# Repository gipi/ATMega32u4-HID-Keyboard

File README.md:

## ATMega32u4 HID Keyboard

### Board Project 2019 - Krishna Mani

This is software for ATMega32u4 or compatible AVR hardware USB chips that
implements a standard-complying HID keyboard using only AVR-LIBC.

I used these for reference when coding:

1. https://www.avrfreaks.net/forum/usb-initialization-problem
2. https://www.pjrc.com/teensy/usb_keyboard.html
3. https://www.usb.org/sites/default/files/documents/hid1_11.pdf
4. https://www.avrfreaks.net/forum/help-properly-initializing-usb-hardware-atmega32u4
5. https://www.beyondlogic.org/usbnutshell/usb1.shtml
6. http://ww1.microchip.com/downloads/en/devicedoc/atmel-7766-8-bit-avr-atmega16u4-32u4_datasheet.pdf
7. https://github.com/arduino/ArduinoCore-avr/blob/master/cores/arduino/USBCore.cpp
8. http://sdphca.ucsd.edu/lab_equip_manuals/usb_20.pdf

Finished Board:

### Hardware

##### Microcontroller

The ATMega32u4 controls the scanning matrix and the USB interface. I chose it
because of its hardware USB interface and because it has enough I/O pins to
support the whole keyboard without needing any multiplexing. It also has enough
flash and SRAM for storing layouts. The 32u4 on the keyboard runs at 16mHz from
an external crystal oscillator with 22pF load capacitors. It is powered directly
from the USB lines with filtering capacitors.

##### PCBs

Initially, I needed to test the main microcontroller circuit of the keyboard to
ensure that it worked and that the USB worked, because I had developed on an
Arduino Leonardo. (boards/ATMegaTestingBoard.brd)

##### ATMega32u4 Circuit

The portion of the board for the ATMega32u4 is fairly standard for this chip and
is similar to the Arduino Leonardo, excluding the power regulators. It consists
of the chip, the oscillator and load caps, the power and layer leds, the reset
switch, the USB connector and data resistors, the ICSP pins, and the filtering
    caps on the underside of the board.

Top / Bottom (boards/Keyboard.brd):

The rest of the board is the scanning matrix. The rows and columns use up the
majority of the I/O on the chip.  The matrix is standard for a keyboard - one
pin of each switch in a column is connected through a diode to every other one
in the column. Then, the remaining pin in each switch is common with the row. I
used through hole diodes because they are much easier to solder. The switches
are standard mechanical keyboard switches, and the footprints are from here:
https://github.com/mknyszek/gateron-eagle To read the matrix, the row pins are
pulled high through internal pull-up resistors. One column at a time is set low,
so that a pressed key would pull the row pin low, signaling a key press at the
current row and column index.

Top / Bottom matrix (boards/Keyboard.brd):

##### Board Assembly

Assembling the board was straightforward except for the SMD components,
specifically the TQFP ATMega32u4. It is really easy to bridge several pads very
quickly, and completely ruin the chip. I soldered these by holding them in place
and tacking down the corners so the chip didn’t move. I used a lot of flux, then
with very little solder dragged the iron across the pins. The USB connector is
also really difficult, I soldered the anchor pins and then the pins. It is
really easy to bridge the pins with the ground enclosure. Using super glue after
ensures that the connector doesn’t snap off when you unplug the cable.

### Code

To compile you need ``cmake``

```
$ mkdir build && cd build
$ cmake -DCMAKE_TOOLCHAIN_FILE=/path/to/cmake-avr/generic-gcc-avr.cmake ..
$ make
```

##### USB

First, the USB controller of the 32u4 is initialized. This is handled in the
function `usb_init()`. The PLL (Phase Locked Loop) is initialized, taking the
external clock as input. It runs at 48mHz and acts as the USB clock. After the
USB controller is initialized, the control endpoint is set up and will receive
setup packets from the host. The setup packets, handled in the ISR
`USB_gen_vect`, elicit responses from the keyboard based on the values of
bmRequestType and bRequest, which determine the type of request. After the host
has requested and received the USB descriptors, and the keyboard has correctly
responded to HID-specific requests, the host can enumerate the device and use it
as an input device.

The key repeat feature of modern keyboards is handled separately from the
standard functions `usb_send()` and `usb_send_keypress()`. If a key is held down
for some period of time, it should be repeated until it is released. This is
    taken care of in the ISR `USB_gen_vect`, specifically when the SOFE (start
    of frame) bit is set. This interrupt triggers at 1kHz, which is how often
    the host sends start of frame packets. If no keypresses have been generated
    since the period time, which is kept track of with keyboard_idle_value and
    current_idle, the entire HID report is resent to facilitate key repeat. The
    period of time the device should wait before resending the report is set
    from the wValue in the HID request SET_IDLE.

##### Matrix Software

The scanning matrix of the keyboard uses the current sourcing and internal
pullups of the I/O ports on the 32u4. Because of the orientation of the diodes,
the columns of the keyboard are set low when they are going to be read. The rows
are always pulled up, meaning that if a key is pressed, it will be pulled low
because the switch is connecting the row and columns. The matrix scanning is
repeated quickly, and changes in key state are recorded in the six-byte USB HID
report. The report is six bytes to support six concurrent key presses. The
keyboard dynamically assigns and removes keys from the report to support
6-key-rollover, and it also resets the reports on layout layer shifts to prevent
strange glitches. The meta and special keys like CTRL, ALT, and SHIFT have their
own byte apart from the report, where each bit represents a different key. This
is according to the USB HID Spec.

The rows and columns of the recorded keypresses are translated into actual
keycodes from the specified layout in `layout.h`. The layout is written from the
standard HID keycodes in `keys.h`. Because the keyboard does not have enough
physical keys to support all the letters, function, and number keys, some keys
are macros that change the mappings of all the keys. These keys are handled
separately and do not generate keypress events on their own. Rather, they update
the current layer that the scanning matrix is reporting keypresses from to
change the keycodes.

### Improvements

1. Changing the routing on PORTD to make it iterable, making the code more readable and cleaner.
2. Using USB-C instead of micro b, meaning that you would not need a dongle for use with newer macs. This would, however, make it much more difficult to solder and the PCB more complicated, since the USB-C connectors have 24 pins.
3. Using the BGA package for the ATMega32u4 so that it could fit in between switches on the underside of the board, meaning that the PCB would only have to be as big as to fit the switches. This would make it more compact.
4. Using symmetrical keycaps so that the keycaps aren’t skewed when using keyboard layouts other than QWERTY.
5. Adding support for a dedicated FN key endpoint and Caps lock and num lock; currently you have to remap function to media keys with a third party tool for the media keys on the keyboard to work on touch bar macs.
6. Move the ICSP connector down, right now you have to bend the power LED up for the connector to make contact with the headers.
7. Route the third layer led to a different I/O port, right now only two of the three LEDs work.

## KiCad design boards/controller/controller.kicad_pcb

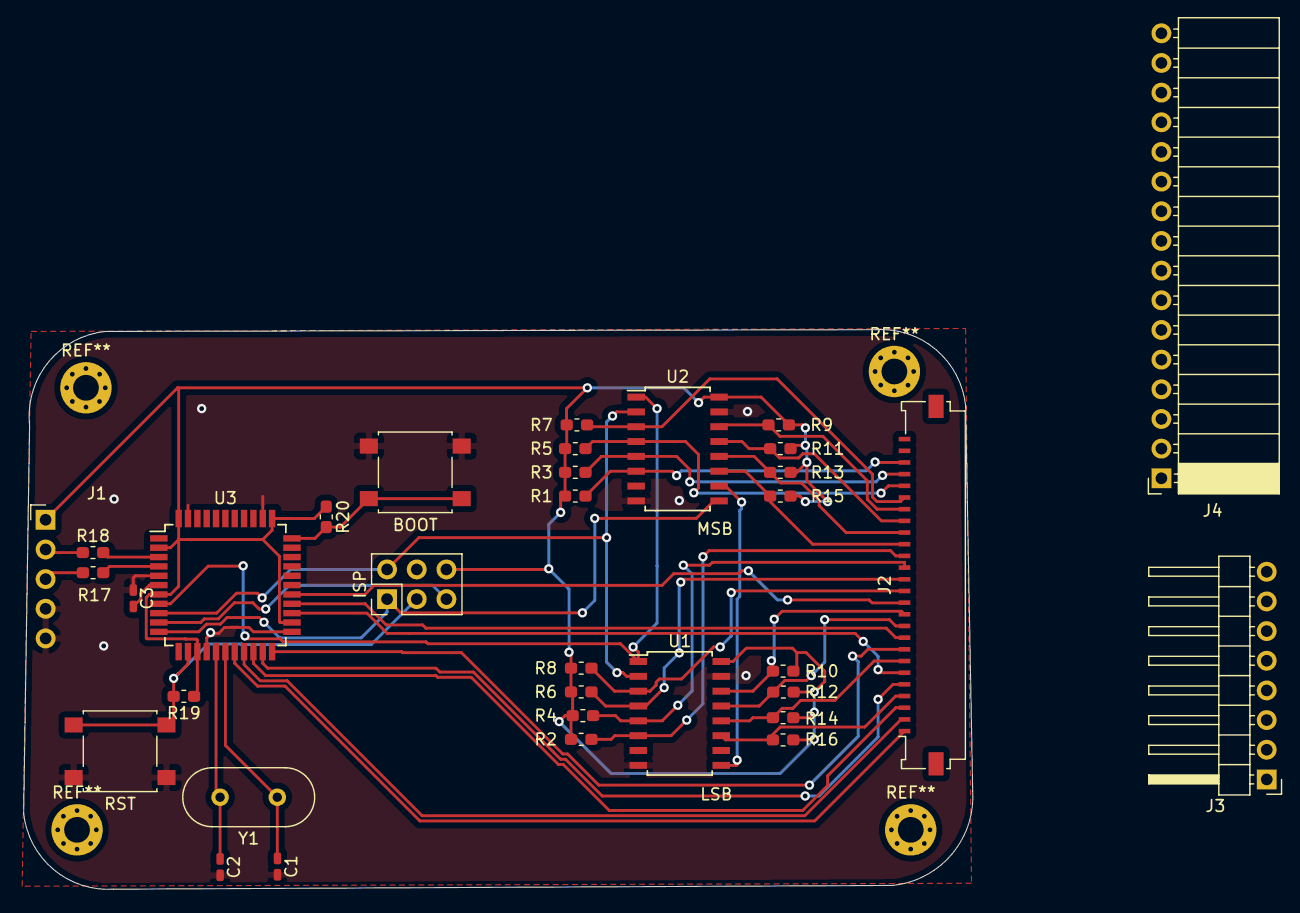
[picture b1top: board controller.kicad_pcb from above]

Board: 2 copper layers, 81.3 x 47.9 mm, 34 parts (0 on the bottom side), 40 nets.

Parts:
BOOT: SW_Push; SW_SPST_B3S-1000
C1, C2: C; C_0402_handSoldering
C3: 1uF; C_0402_handSoldering
ISP: Conn_02x03_Counter_Clockwise_MountingPin; PinHeader_2x03_P2.54mm_Vertical
J1: USB_A; PinHeader_1x05_P2.54mm_Horizontal
J2: Conn_01x26; Molex_200528-0260_1x26-1MP_P1.00mm_Horizontal
J3: Conn_01x08; PinHeader_1x08_P2.54mm_Horizontal
J4: Conn_01x16; PinSocket_1x16_P2.54mm_Horizontal
R1, R2, R3, R4, R5, R6, R7, R8, R9, R10, R11, R12, R13, R14, R15, R16, R17, R18, R19, R20: R; R_0603_1608Metric_Pad1.05x0.95mm_HandSolder
RST: SW_Push; SW_SPST_B3S-1000
U1, U2: 74LS165; SOIC-16W_5.3x10.2mm_P1.27mm
U3: ATmega32U4-AU; TQFP-44_10x10mm_P0.8mm
Y1: Crystal; Crystal_HC18-U_Vertical

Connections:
/I0: J2.1, J3.1, U3.18
/I1: J2.2, J3.2, U3.19
/I2: J2.3, J3.3, U3.20
/I3: J2.5, J3.4, U3.21
/I4: J2.6, J3.5, U3.25
/I5: J2.8, J3.6, U3.22
/I6: J2.9, J3.7, U3.26
/I7: J2.12, J3.8, U3.27
/O0: J2.4, J4.1, R16.2, U1.11
/O1: J2.7, J4.2, R14.2, U1.12
/O2: J2.10, J4.3, R12.2, U1.13
/O3: J2.11, J4.4, R10.2, U1.14
/O4: J2.13, J4.5, R8.2, U1.3
/O5: J2.14, J4.6, R6.2, U1.4
/O6: J2.15, J4.7, R4.2, U1.5
/O7: J2.16, J4.8, R2.2, U1.6
/O8: J2.17, J4.9, R15.2, U2.11
/O9: J2.18, J4.10, R13.2, U2.12
/O10: J2.19, J4.11, R11.2, U2.13
/O11: J2.20, J4.12, R9.2, U2.14
/O12: J2.21, J4.13, R7.2, U2.3
/O13: J2.22, J4.14, R5.2, U2.4
/O14: J2.23, J4.15, R3.2, U2.5
/O15: J2.24, J4.16, R1.2, U2.6
BOOT: BOOT.1, R20.2, U3.33
GND: BOOT.2, C1.2, C2.2, C3.1, ISP.4, J1.4, J1.5, RST.1, U1.8, U1.15, U2.8, U2.15, U3.5, U3.15, U3.23, U3.35, U3.43
MISO: ISP.1, U2.9, U3.11
MOSI: ISP.5, U3.10
unnamed: C1.1, U3.17, Y1.1
unnamed: C2.1, U3.16, Y1.2
unnamed: C3.2, U3.6
unnamed: J1.2, R18.1
unnamed: J1.3, R17.1
unnamed: R17.2, U3.4
unnamed: R18.2, U3.3
unnamed: U1.9, U2.10
RESET: ISP.3, R19.2, RST.2, U3.13
SCK: ISP.2, U1.2, U2.2, U3.9
SS: U1.1, U2.1, U3.8
VCC: ISP.6, J1.1, R1.1, R2.1, R3.1, R4.1, R5.1, R6.1, R7.1, R8.1, R9.1, R10.1, R11.1, R12.1, R13.1, R14.1, R15.1, R16.1, R19.1, R20.1, U1.16, U2.16, U3.2, U3.7, U3.14, U3.24, U3.34, U3.44

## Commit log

2021-04-16 Rework CMakeLists.txt to use cmake-avr.
2021-04-16 Improve README.
2021-04-16 Remove #define.
    It is defined already by the cmake.
2021-04-16 Fix compilation warning.
2021-06-12 Factorize code.
2021-06-14 Add missing key definitions.
2021-06-24 First working keyboard.
2021-06-24 First draft for the controller PCB.
